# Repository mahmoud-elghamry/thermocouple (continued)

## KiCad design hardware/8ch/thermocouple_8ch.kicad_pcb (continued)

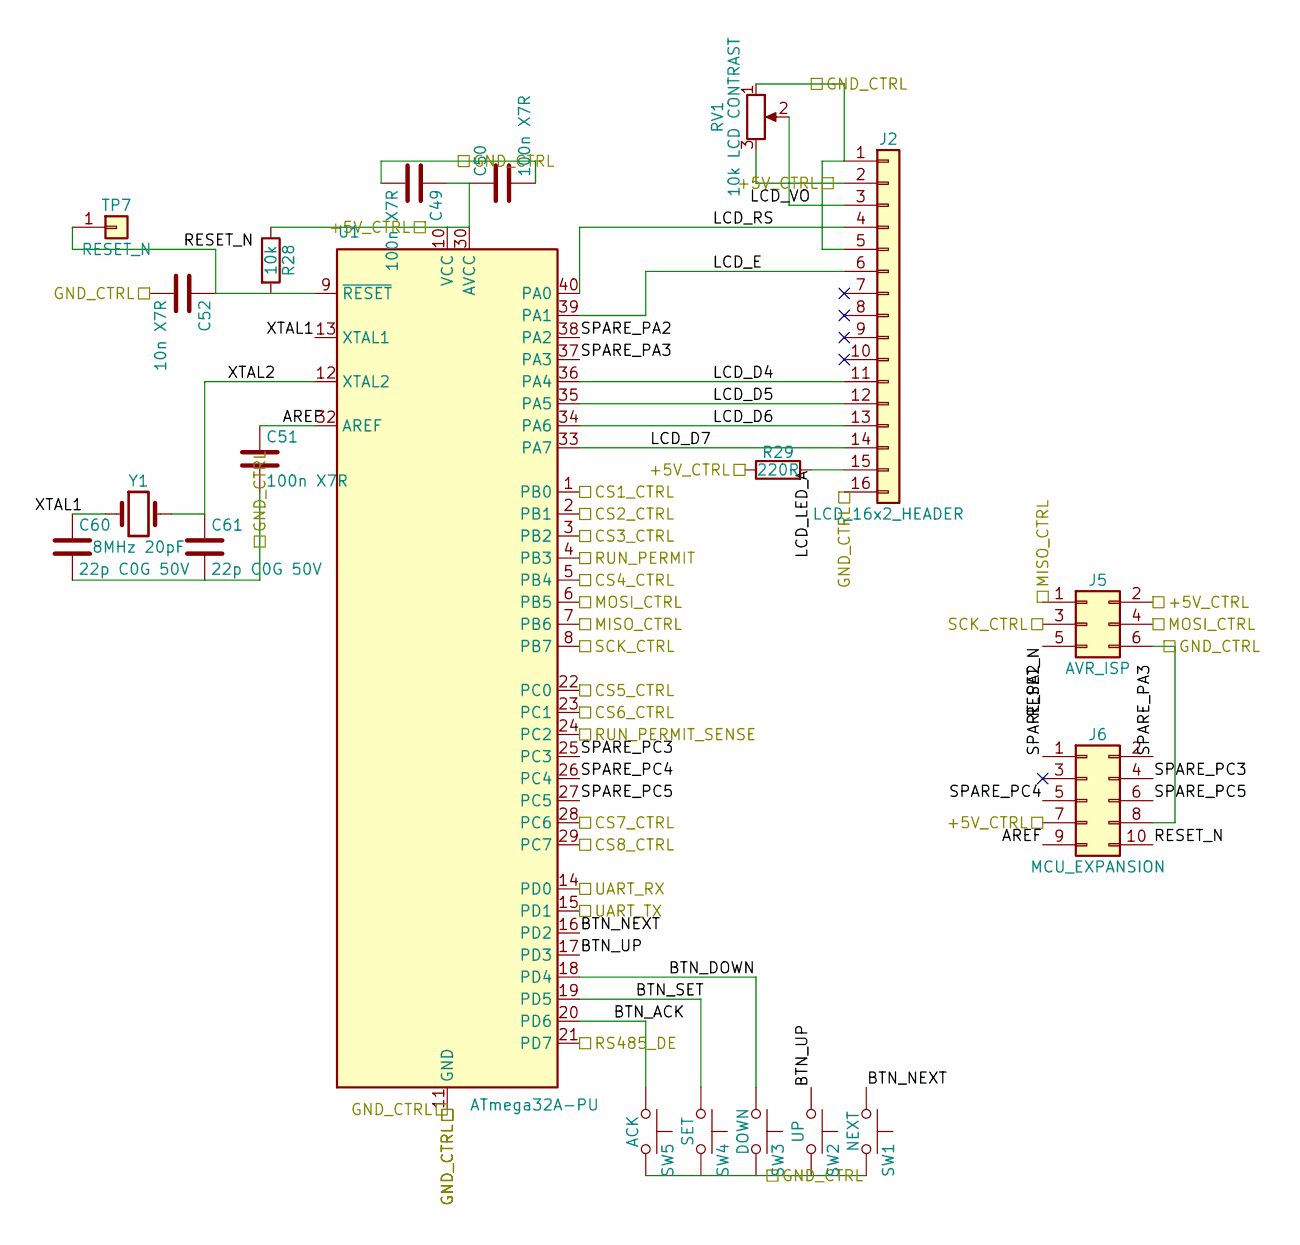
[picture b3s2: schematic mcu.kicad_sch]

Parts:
C49, C50, C51: 100n X7R; C_0805_2012Metric; MPN CC0805KRX7R9BB104; LCSC C49678
C52: 10n X7R; C_0805_2012Metric; MPN CL21B103KBANNNC; LCSC C1710
C60, C61: 22p C0G 50V; C_0805_2012Metric; MPN CL21C220JBANNNC; LCSC C1804
J2: LCD_16x2_HEADER; PinHeader_1x16_P2.54mm_Vertical; MPN ZX-PZ2.54-1-16PZZ; LCSC C7501270
J5: AVR_ISP; PinHeader_2x03_P2.54mm_Vertical; MPN PZ254V-12-6P; LCSC C492420
J6: MCU_EXPANSION; PinHeader_2x05_P2.54mm_Vertical; MPN PZ254V-12-10P; LCSC C492422
R28: 10k; R_0805_2012Metric; MPN 0805W8F1002T5E; LCSC C17414
R29: 220R; R_0805_2012Metric; MPN 0805W8F2200T5E; LCSC C17557
RV1: 10k LCD CONTRAST; Potentiometer_Bourns_3296W_Vertical; MPN 3296W-1-103LF; LCSC C34846
SW1: NEXT; SW_PUSH_6mm; MPN TS665CJ; LCSC C393938
SW2: UP; SW_PUSH_6mm; MPN TS665CJ; LCSC C393938
SW3: DOWN; SW_PUSH_6mm; MPN TS665CJ; LCSC C393938
SW4: SET; SW_PUSH_6mm; MPN TS665CJ; LCSC C393938
SW5: ACK; SW_PUSH_6mm; MPN TS665CJ; LCSC C393938
TP7: RESET_N; TestPoint_THTPad_D2.0mm_Drill1.0mm
U1: ATmega32A-PU; DIP-40_W15.24mm_Socket; MPN ATMEGA32A-PU; LCSC C12703
Y1: 8MHz 20pF; Crystal_SMD_HC49-SD; MPN X49SM8MSD2SC; LCSC C12674

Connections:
/+5V_CTRL: C49.1, C50.1, J2.2, J5.2, J6.7, R28.1, R29.1, RV1.3, U1.10 (VCC), U1.30 (AVCC); also elsewhere on the board
/CS1_CTRL: U1.1 (PB0); also elsewhere on the board
/CS2_CTRL: U1.2 (PB1); also elsewhere on the board
/CS3_CTRL: U1.3 (PB2); also elsewhere on the board
/CS4_CTRL: U1.5 (PB4); also elsewhere on the board
/CS5_CTRL: U1.22 (PC0); also elsewhere on the board
/CS6_CTRL: U1.23 (PC1); also elsewhere on the board
/CS7_CTRL: U1.28 (PC6); also elsewhere on the board
/CS8_CTRL: U1.29 (PC7); also elsewhere on the board
/GND_CTRL: C49.2, C50.2, C51.2, C52.2, C60.2, C61.2, J2.1, J2.5, J2.16, J5.6, J6.8, RV1.1, SW1.2, SW2.2, SW3.2, SW4.2, SW5.2, U1.11 (GND), U1.31 (GND); also elsewhere on the board
/MCU/AREF: C51.1, J6.9, U1.32 (AREF)
/MCU/BTN_ACK: SW5.1, U1.20 (PD6)
/MCU/BTN_DOWN: SW3.1, U1.18 (PD4)
/MCU/BTN_NEXT: SW1.1, U1.16 (PD2)
/MCU/BTN_SET: SW4.1, U1.19 (PD5)
/MCU/BTN_UP: SW2.1, U1.17 (PD3)
/MCU/LCD_D4: J2.11, U1.36 (PA4)
/MCU/LCD_D5: J2.12, U1.35 (PA5)
/MCU/LCD_D6: J2.13, U1.34 (PA6)
/MCU/LCD_D7: J2.14, U1.33 (PA7)
/MCU/LCD_E: J2.6, U1.39 (PA1)
/MCU/LCD_LED_A: J2.15, R29.2
/MCU/LCD_RS: J2.4, U1.40 (PA0)
/MCU/LCD_VO: J2.3, RV1.2
/MCU/RESET_N: C52.1, J5.5, J6.10, R28.2, TP7.1 (Pin_1_1), U1.9 (~RESET)
/MCU/SPARE_PA2: J6.1, U1.38 (PA2)
/MCU/SPARE_PA3: J6.2, U1.37 (PA3)
/MCU/SPARE_PC3: J6.4, U1.25 (PC3)
/MCU/SPARE_PC4: J6.5, U1.26 (PC4)
/MCU/SPARE_PC5: J6.6, U1.27 (PC5)
/MCU/XTAL1: C60.1, U1.13 (XTAL1), Y1.1
/MCU/XTAL2: C61.1, U1.12 (XTAL2), Y1.2
/MISO_CTRL: J5.1, U1.7 (PB6); also elsewhere on the board
/MOSI_CTRL: J5.4, U1.6 (PB5); also elsewhere on the board
/RS485_DE: U1.21 (PD7); also elsewhere on the board
/RUN_PERMIT: U1.4 (PB3); also elsewhere on the board
/RUN_PERMIT_SENSE: U1.24 (PC2); also elsewhere on the board
/SCK_CTRL: J5.3, U1.8 (PB7); also elsewhere on the board
/UART_RX: U1.14 (PD0); also elsewhere on the board
/UART_TX: U1.15 (PD1); also elsewhere on the board

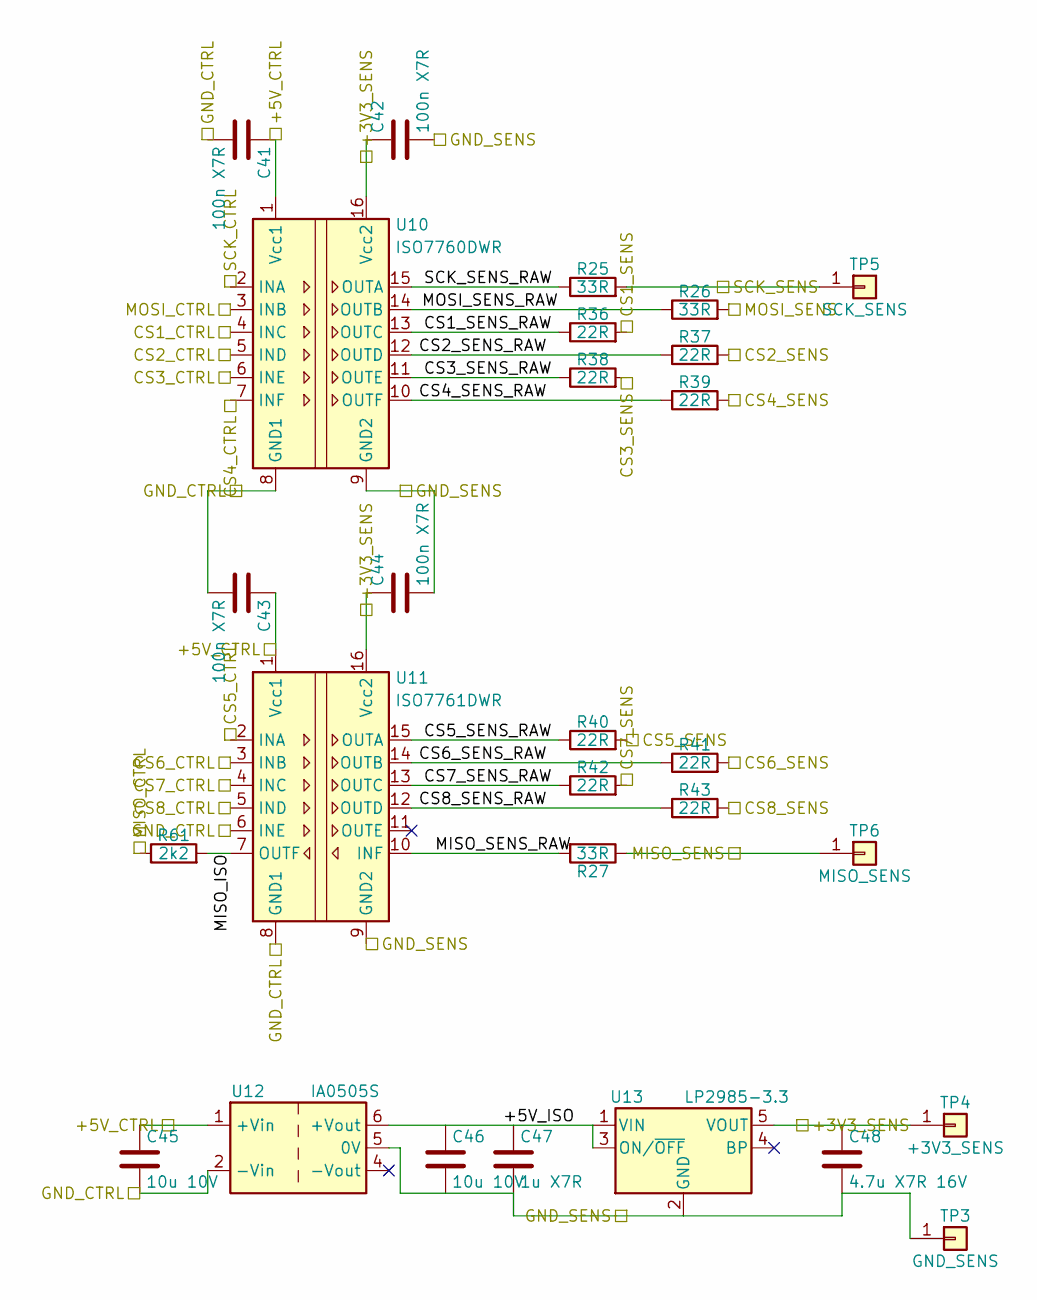
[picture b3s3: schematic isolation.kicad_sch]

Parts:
C41, C42, C43, C44: 100n X7R; C_0805_2012Metric; MPN CC0805KRX7R9BB104; LCSC C49678
C45, C46: 10u 10V; C_0805_2012Metric; MPN CL21A106KAYNNNE; LCSC C15850
C47: 1u X7R; C_0805_2012Metric; MPN CL21B105KBFNNNE; LCSC C28323
C48: 4.7u X7R 16V; C_0805_2012Metric; MPN CGA0805X7R475K350MT; LCSC C6119943
R25, R26, R27: 33R; R_0805_2012Metric; MPN 0805W8F330JT5E; LCSC C17634
R36, R37, R38, R39, R40, R41, R42, R43: 22R; R_0805_2012Metric; MPN 0805W8F220JT5E; LCSC C17561
R61: 2k2; R_0805_2012Metric; MPN 0805W8F2201T5E; LCSC C17520
TP3: GND_SENS; TestPoint_THTPad_D2.0mm_Drill1.0mm
TP4: +3V3_SENS; TestPoint_THTPad_D2.0mm_Drill1.0mm
TP5: SCK_SENS; TestPoint_THTPad_D2.0mm_Drill1.0mm
TP6: MISO_SENS; TestPoint_THTPad_D2.0mm_Drill1.0mm
U10: ISO7760DWR; SOIC-16W_7.5x10.3mm_P1.27mm; MPN ISO7760DWR; LCSC C882724
U11: ISO7761DWR; SOIC-16W_7.5x10.3mm_P1.27mm; MPN ISO7761DWR; LCSC C2871529
U12: IA0505S; Converter_DCDC_XP_POWER-IAxxxxS_THT; MPN IA0505S
U13: LP2985-3.3; SOT-23-5; MPN LP2985IM5X-3.3/NOPB

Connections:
/+3V3_SENS: C42.1, C44.1, C48.1, TP4.1 (Pin_1_1), U10.16 (Vcc2), U11.16 (Vcc2), U13.5 (VOUT); also elsewhere on the board
/+5V_CTRL: C41.1, C43.1, C45.1, U10.1 (Vcc1), U11.1 (Vcc1), U12.1 (+Vin); also elsewhere on the board
/CS1_CTRL: U10.4 (INC); also elsewhere on the board
/CS1_SENS: R36.2; also elsewhere on the board
/CS2_CTRL: U10.5 (IND); also elsewhere on the board
/CS2_SENS: R37.2; also elsewhere on the board
/CS3_CTRL: U10.6 (INE); also elsewhere on the board
/CS3_SENS: R38.2; also elsewhere on the board
/CS4_CTRL: U10.7 (INF); also elsewhere on the board
/CS4_SENS: R39.2; also elsewhere on the board
/CS5_CTRL: U11.2 (INA); also elsewhere on the board
/CS5_SENS: R40.2; also elsewhere on the board
/CS6_CTRL: U11.3 (INB); also elsewhere on the board
/CS6_SENS: R41.2; also elsewhere on the board
/CS7_CTRL: U11.4 (INC); also elsewhere on the board
/CS7_SENS: R42.2; also elsewhere on the board
/CS8_CTRL: U11.5 (IND); also elsewhere on the board
/CS8_SENS: R43.2; also elsewhere on the board
/GND_CTRL: C41.2, C43.2, C45.2, U10.8 (GND1), U11.6 (INE), U11.8 (GND1), U12.2 (-Vin); also elsewhere on the board
/GND_SENS: C42.2, C44.2, C46.2, C47.2, C48.2, TP3.1 (Pin_1_1), U10.9 (GND2), U11.9 (GND2), U12.5 (0V), U13.2 (GND); also elsewhere on the board
/ISOLATION/+5V_ISO: C46.1, C47.1, U12.6 (+Vout), U13.1 (VIN), U13.3 (ON/~OFF)
/ISOLATION/CS1_SENS_RAW: R36.1, U10.13 (OUTC)
/ISOLATION/CS2_SENS_RAW: R37.1, U10.12 (OUTD)
/ISOLATION/CS3_SENS_RAW: R38.1, U10.11 (OUTE)
/ISOLATION/CS4_SENS_RAW: R39.1, U10.10 (OUTF)
/ISOLATION/CS5_SENS_RAW: R40.1, U11.15 (OUTA)
/ISOLATION/CS6_SENS_RAW: R41.1, U11.14 (OUTB)
/ISOLATION/CS7_SENS_RAW: R42.1, U11.13 (OUTC)
/ISOLATION/CS8_SENS_RAW: R43.1, U11.12 (OUTD)
/ISOLATION/MISO_ISO: R61.2, U11.7 (OUTF)
/ISOLATION/MISO_SENS_RAW: R27.2, U11.10 (INF)
/ISOLATION/MOSI_SENS_RAW: R26.1, U10.14 (OUTB)
/ISOLATION/SCK_SENS_RAW: R25.1, U10.15 (OUTA)
/MISO_CTRL: R61.1; also elsewhere on the board
/MISO_SENS: R27.1, TP6.1 (Pin_1_1); also elsewhere on the board
/MOSI_CTRL: U10.3 (INB); also elsewhere on the board
/MOSI_SENS: R26.2; also elsewhere on the board
/SCK_CTRL: U10.2 (INA); also elsewhere on the board
/SCK_SENS: R25.2, TP5.1 (Pin_1_1); also elsewhere on the board

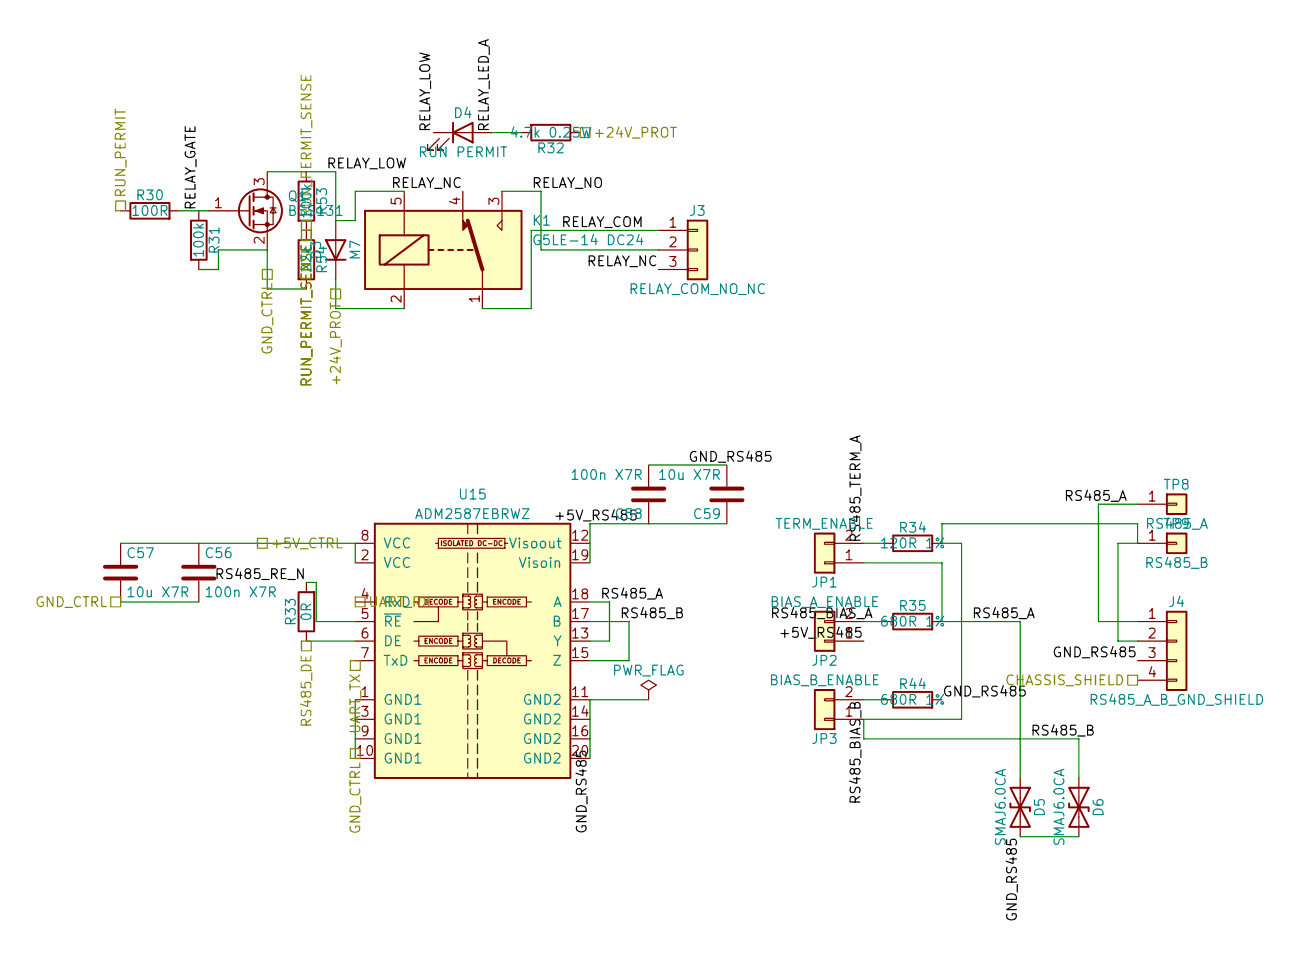
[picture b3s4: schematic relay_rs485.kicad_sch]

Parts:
C56, C58: 100n X7R; C_0805_2012Metric; MPN CC0805KRX7R9BB104; LCSC C49678
C57, C59: 10u X7R; C_0805_2012Metric; MPN CL21B106KOQNNNE; LCSC C95841
D3: M7; D_SMA; MPN M7; LCSC C95872
D4: RUN PERMIT; LED_D3.0mm; MPN 3A4GUD; LCSC C52034646
D5, D6: SMAJ6.0CA; D_SMA; MPN SMAJ6.0CA; LCSC C19077526
J3: RELAY_COM_NO_NC; TerminalBlock_Phoenix_MKDS-1,5-3_1x03_P5.00mm_Horizontal; MPN WJ128V-5.0-3P; LCSC C8270
J4: RS485_A_B_GND_SHIELD; TerminalBlock_Phoenix_MKDS-1,5-4_1x04_P5.00mm_Horizontal; MPN WJ128V-5.0-04P-14-00A; LCSC C192769
JP1: TERM_ENABLE; PinHeader_1x02_P2.54mm_Vertical; MPN PZ254V-11-02P; LCSC C492401
JP2: BIAS_A_ENABLE; PinHeader_1x02_P2.54mm_Vertical; MPN PZ254V-11-02P; LCSC C492401
JP3: BIAS_B_ENABLE; PinHeader_1x02_P2.54mm_Vertical; MPN PZ254V-11-02P; LCSC C492401
K1: G5LE-14 DC24; Relay_SPDT_Omron-G5LE-1; MPN G5LE-14 DC24; LCSC C116965
Q1: BSS131; SOT-23; MPN BSS131H6327XTSA1; LCSC C151498
R30: 100R; R_0805_2012Metric; MPN 0805W8F1000T5E; LCSC C17408
R31, R53: 100k; R_0805_2012Metric; MPN 0805W8F1003T5E; LCSC C149504
R32: 4.7k 0.25W; R_0805_2012Metric; MPN RK73H2ATTD4701F; LCSC C276229
R33: 0R; R_0805_2012Metric; MPN 0805W8F0000T5E; LCSC C17477
R34: 120R 1%; R_0805_2012Metric; MPN 0805W8F1200T5E; LCSC C17437
R35, R44: 680R 1%; R_0805_2012Metric; MPN 0805W8F6800T5E; LCSC C17798
R54: 22k; R_0805_2012Metric; MPN 0805W8F2202T5E; LCSC C17560
TP8: RS485_A; TestPoint_THTPad_D2.0mm_Drill1.0mm
TP9: RS485_B; TestPoint_THTPad_D2.0mm_Drill1.0mm
U15: ADM2587EBRWZ; SOIC-20W_7.5x12.8mm_P1.27mm; MPN ADM2587EBRWZ-REEL7; LCSC C12081

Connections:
/+5V_CTRL: C56.1, C57.1, U15.2 (VCC), U15.8 (VCC); also elsewhere on the board
/+24V_PROT: D3.1 (K), K1.2, R32.1; also elsewhere on the board
/CHASSIS_SHIELD: J4.4; also elsewhere on the board
/GND_CTRL: C56.2, C57.2, Q1.2 (S), R31.2, R54.2, U15.1 (GND1), U15.3 (GND1), U15.9 (GND1), U15.10 (GND1); also elsewhere on the board
/RELAY_RS485/+5V_RS485: C58.1, C59.1, JP2.1, U15.12 (Visoout), U15.19 (Visoin)
/RELAY_RS485/GND_RS485: C58.2, C59.2, D5.2 (A2), D6.2 (A2), J4.3, R44.2, U15.11 (GND2), U15.14 (GND2), U15.16 (GND2), U15.20 (GND2)
/RELAY_RS485/RELAY_COM: J3.1, K1.1
/RELAY_RS485/RELAY_GATE: Q1.1 (G), R30.2, R31.1
/RELAY_RS485/RELAY_LED_A: D4.2 (A), R32.2
/RELAY_RS485/RELAY_LOW: D3.2 (A), D4.1 (K), K1.5, Q1.3 (D), R53.1
/RELAY_RS485/RELAY_NC: J3.3, K1.4
/RELAY_RS485/RELAY_NO: J3.2, K1.3
/RELAY_RS485/RS485_A: D5.1 (A1), J4.1, JP1.1, R35.2, TP8.1 (Pin_1_1), U15.13 (Y), U15.18 (A)
/RELAY_RS485/RS485_B: D6.1 (A1), J4.2, JP3.1, R34.2, TP9.1 (Pin_1_1), U15.15 (Z), U15.17 (B)
/RELAY_RS485/RS485_BIAS_A: JP2.2, R35.1
/RELAY_RS485/RS485_BIAS_B: JP3.2, R44.1
/RELAY_RS485/RS485_RE_N: R33.2, U15.5 (~RE)
/RELAY_RS485/RS485_TERM_A: JP1.2, R34.1
/RS485_DE: R33.1, U15.6 (DE); also elsewhere on the board
/RUN_PERMIT: R30.1; also elsewhere on the board
/RUN_PERMIT_SENSE: R53.2, R54.1; also elsewhere on the board
/UART_RX: U15.4 (RxD); also elsewhere on the board
/UART_TX: U15.7 (TxD); also elsewhere on the board

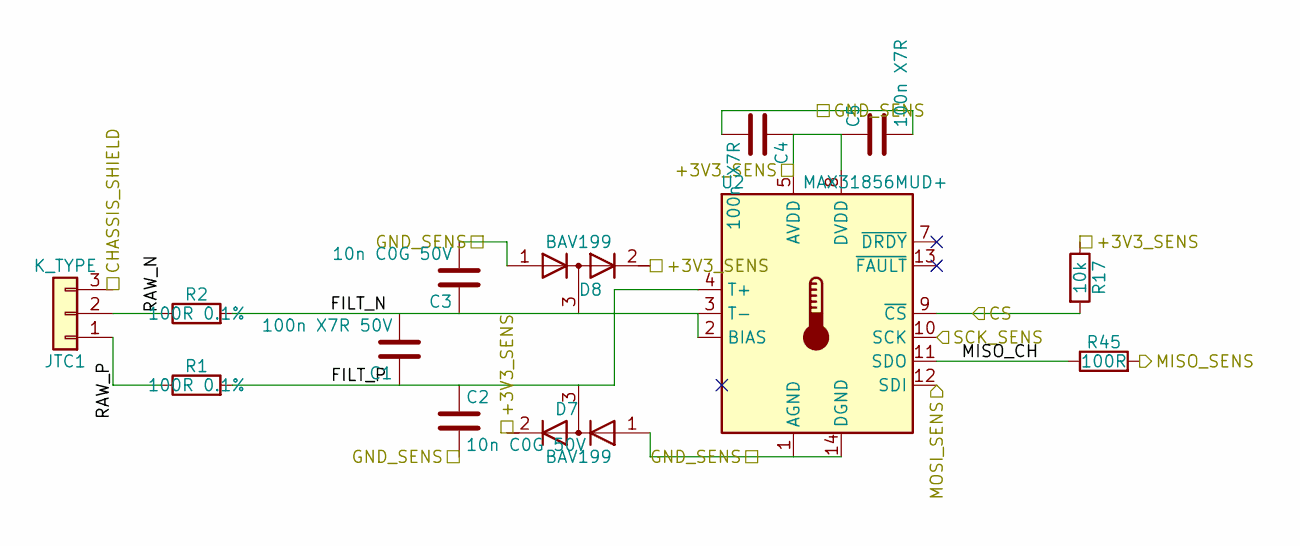
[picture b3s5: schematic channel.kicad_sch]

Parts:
C1: 100n X7R 50V; C_0805_2012Metric; MPN CC0805KRX7R9BB104; LCSC C49678
C2, C3: 10n C0G 50V; C_0805_2012Metric; MPN GRM2195C1H103JA01D; LCSC C97905
C4, C5: 100n X7R; C_0805_2012Metric; MPN CC0805KRX7R9BB104; LCSC C49678
D7, D8: BAV199; SOT-23; MPN BAV199; LCSC C5184419
JTC1: K_TYPE; TerminalBlock_Phoenix_MKDS-1,5-3_1x03_P5.00mm_Horizontal; MPN WJ128V-5.0-3P; LCSC C8270
R1, R2: 100R 0.1%; R_0805_2012Metric; MPN RT0805BRD07100RL; LCSC C110773
R17: 10k; R_0805_2012Metric; MPN 0805W8F1002T5E; LCSC C17414
R45: 100R; R_0805_2012Metric; MPN 0805W8F1000T5E; LCSC C17408
U2: MAX31856MUD+; TSSOP-14_4.4x5mm_P0.65mm; MPN MAX31856MUD+

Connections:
/+3V3_SENS: C4.1, C5.1, D7.2 (K), D8.2 (K), R17.1, U2.5 (AVDD), U2.8 (DVDD); also elsewhere on the board
/CHASSIS_SHIELD: JTC1.3; also elsewhere on the board
/CS1_SENS: R17.2, U2.9 (~CS); also elsewhere on the board
/GND_SENS: C2.2, C3.2, C4.2, C5.2, D7.1 (A), D8.1 (A), U2.1 (AGND), U2.14 (DGND); also elsewhere on the board
/MISO_SENS: R45.2; also elsewhere on the board
/MOSI_SENS: U2.12 (SDI); also elsewhere on the board
/SCK_SENS: U2.10 (SCK); also elsewhere on the board
/TC1/FILT_N: C1.2, C3.1, D8.3 (common), R2.2, U2.2 (BIAS), U2.3 (T-)
/TC1/FILT_P: C1.1, C2.1, D7.3 (common), R1.2, U2.4 (T+)
/TC1/MISO_CH: R45.1, U2.11 (SDO)
/TC1/RAW_N: JTC1.2, R2.1
/TC1/RAW_P: JTC1.1, R1.1

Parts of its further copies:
C6, C11, C16, C21, C26, C31, C36: 100n X7R 50V; C_0805_2012Metric; MPN CC0805KRX7R9BB104; LCSC C49678
C7, C8, C12, C13, C17, C18, C22, C23, C27, C28, C32, C33, C37, C38: 10n C0G 50V; C_0805_2012Metric; MPN GRM2195C1H103JA01D; LCSC C97905
C9, C10, C14, C15, C19, C20, C24, C25, C29, C30, C34, C35, C39, C40: 100n X7R; C_0805_2012Metric; MPN CC0805KRX7R9BB104; LCSC C49678
D9, D10, D11, D12, D13, D14, D15, D16, D17, D18, D19, D20, D21, D22: BAV199; SOT-23; MPN BAV199; LCSC C5184419
JTC2, JTC3, JTC4, JTC5, JTC6, JTC7, JTC8: K_TYPE; TerminalBlock_Phoenix_MKDS-1,5-3_1x03_P5.00mm_Horizontal; MPN WJ128V-5.0-3P; LCSC C8270
R3, R4, R5, R6, R7, R8, R9, R10, R11, R12, R13, R14, R15, R16: 100R 0.1%; R_0805_2012Metric; MPN RT0805BRD07100RL; LCSC C110773
R18, R19, R20, R21, R22, R23, R24: 10k; R_0805_2012Metric; MPN 0805W8F1002T5E; LCSC C17414
R46, R47, R48, R49, R50, R51, R52: 100R; R_0805_2012Metric; MPN 0805W8F1000T5E; LCSC C17408
U3, U4, U5, U6, U7, U8, U9: MAX31856MUD+; TSSOP-14_4.4x5mm_P0.65mm; MPN MAX31856MUD+

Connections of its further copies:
/+3V3_SENS: C9.1, C10.1, C14.1, C15.1, C19.1, C20.1, C24.1, C25.1, C29.1, C30.1, C34.1, C35.1, C39.1, C40.1, D9.2 (K), D10.2 (K), D11.2 (K), D12.2 (K), D13.2 (K), D14.2 (K), D15.2 (K), D16.2 (K), D17.2 (K), D18.2 (K), D19.2 (K), D20.2 (K), D21.2 (K), D22.2 (K), R18.1, R19.1, R20.1, R21.1, R22.1, R23.1, R24.1, U3.5 (AVDD), U3.8 (DVDD), U4.5 (AVDD), U4.8 (DVDD), U5.5 (AVDD), U5.8 (DVDD), U6.5 (AVDD), U6.8 (DVDD), U7.5 (AVDD), U7.8 (DVDD), U8.5 (AVDD), U8.8 (DVDD), U9.5 (AVDD), U9.8 (DVDD); also elsewhere on the board
/CHASSIS_SHIELD: JTC2.3, JTC3.3, JTC4.3, JTC5.3, JTC6.3, JTC7.3, JTC8.3; also elsewhere on the board
/CS2_SENS: R18.2, U3.9 (~CS); also elsewhere on the board
/CS3_SENS: R19.2, U4.9 (~CS); also elsewhere on the board
/CS4_SENS: R20.2, U5.9 (~CS); also elsewhere on the board
/CS5_SENS: R21.2, U6.9 (~CS); also elsewhere on the board
/CS6_SENS: R22.2, U7.9 (~CS); also elsewhere on the board
/CS7_SENS: R23.2, U8.9 (~CS); also elsewhere on the board
/CS8_SENS: R24.2, U9.9 (~CS); also elsewhere on the board
/GND_SENS: C7.2, C8.2, C9.2, C10.2, C12.2, C13.2, C14.2, C15.2, C17.2, C18.2, C19.2, C20.2, C22.2, C23.2, C24.2, C25.2, C27.2, C28.2, C29.2, C30.2, C32.2, C33.2, C34.2, C35.2, C37.2, C38.2, C39.2, C40.2, D9.1 (A), D10.1 (A), D11.1 (A), D12.1 (A), D13.1 (A), D14.1 (A), D15.1 (A), D16.1 (A), D17.1 (A), D18.1 (A), D19.1 (A), D20.1 (A), D21.1 (A), D22.1 (A), U3.1 (AGND), U3.14 (DGND), U4.1 (AGND), U4.14 (DGND), U5.1 (AGND), U5.14 (DGND), U6.1 (AGND), U6.14 (DGND), U7.1 (AGND), U7.14 (DGND), U8.1 (AGND), U8.14 (DGND), U9.1 (AGND), U9.14 (DGND); also elsewhere on the board
/MISO_SENS: R46.2, R47.2, R48.2, R49.2, R50.2, R51.2, R52.2; also elsewhere on the board
/MOSI_SENS: U3.12 (SDI), U4.12 (SDI), U5.12 (SDI), U6.12 (SDI), U7.12 (SDI), U8.12 (SDI), U9.12 (SDI); also elsewhere on the board
/SCK_SENS: U3.10 (SCK), U4.10 (SCK), U5.10 (SCK), U6.10 (SCK), U7.10 (SCK), U8.10 (SCK), U9.10 (SCK); also elsewhere on the board
/TC2/FILT_N: C6.2, C8.1, D10.3 (common), R4.2, U3.2 (BIAS), U3.3 (T-)
/TC2/FILT_P: C6.1, C7.1, D9.3 (common), R3.2, U3.4 (T+)
/TC2/MISO_CH: R46.1, U3.11 (SDO)
/TC2/RAW_N: JTC2.2, R4.1
/TC2/RAW_P: JTC2.1, R3.1
/TC3/FILT_N: C11.2, C13.1, D12.3 (common), R6.2, U4.2 (BIAS), U4.3 (T-)
/TC3/FILT_P: C11.1, C12.1, D11.3 (common), R5.2, U4.4 (T+)
/TC3/MISO_CH: R47.1, U4.11 (SDO)
/TC3/RAW_N: JTC3.2, R6.1
/TC3/RAW_P: JTC3.1, R5.1
/TC4/FILT_N: C16.2, C18.1, D14.3 (common), R8.2, U5.2 (BIAS), U5.3 (T-)
/TC4/FILT_P: C16.1, C17.1, D13.3 (common), R7.2, U5.4 (T+)
/TC4/MISO_CH: R48.1, U5.11 (SDO)
/TC4/RAW_N: JTC4.2, R8.1
/TC4/RAW_P: JTC4.1, R7.1
/TC5/FILT_N: C21.2, C23.1, D16.3 (common), R10.2, U6.2 (BIAS), U6.3 (T-)
/TC5/FILT_P: C21.1, C22.1, D15.3 (common), R9.2, U6.4 (T+)
/TC5/MISO_CH: R49.1, U6.11 (SDO)
/TC5/RAW_N: JTC5.2, R10.1
/TC5/RAW_P: JTC5.1, R9.1
/TC6/FILT_N: C26.2, C28.1, D18.3 (common), R12.2, U7.2 (BIAS), U7.3 (T-)
/TC6/FILT_P: C26.1, C27.1, D17.3 (common), R11.2, U7.4 (T+)
/TC6/MISO_CH: R50.1, U7.11 (SDO)
/TC6/RAW_N: JTC6.2, R12.1
/TC6/RAW_P: JTC6.1, R11.1
/TC7/FILT_N: C31.2, C33.1, D20.3 (common), R14.2, U8.2 (BIAS), U8.3 (T-)
/TC7/FILT_P: C31.1, C32.1, D19.3 (common), R13.2, U8.4 (T+)
/TC7/MISO_CH: R51.1, U8.11 (SDO)
/TC7/RAW_N: JTC7.2, R14.1
/TC7/RAW_P: JTC7.1, R13.1
/TC8/FILT_N: C36.2, C38.1, D22.3 (common), R16.2, U9.2 (BIAS), U9.3 (T-)
/TC8/FILT_P: C36.1, C37.1, D21.3 (common), R15.2, U9.4 (T+)
/TC8/MISO_CH: R52.1, U9.11 (SDO)
/TC8/RAW_N: JTC8.2, R16.1
/TC8/RAW_P: JTC8.1, R15.1

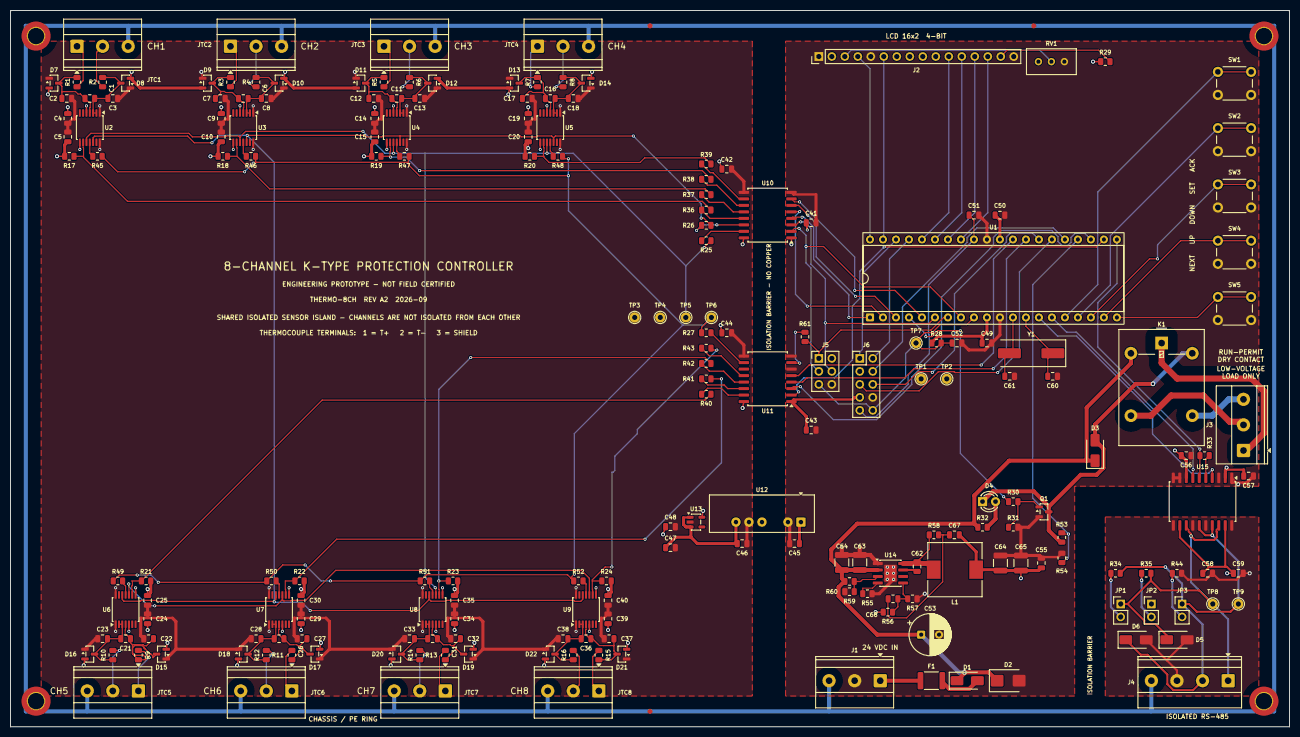
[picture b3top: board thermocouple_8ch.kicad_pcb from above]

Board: 4 copper layers, 250.0 x 140.0 mm, 209 parts (0 on the bottom side), 130 nets.

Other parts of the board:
FID1: FID1; Fiducial_1mm_Mask2mm
FID2: FID2; Fiducial_1mm_Mask2mm
FID3: FID3; Fiducial_1mm_Mask2mm
H1: H1; MountingHole_3.2mm_M3_ISO7380_Pad_TopBottom
H2: H2; MountingHole_3.2mm_M3_ISO7380_Pad_TopBottom
H3: H3; MountingHole_3.2mm_M3_ISO7380_Pad_TopBottom
H4: H4; MountingHole_3.2mm_M3_ISO7380_Pad_TopBottom

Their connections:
/CHASSIS_SHIELD: H1.1, H2.1, H3.1, H4.1; also elsewhere on the board

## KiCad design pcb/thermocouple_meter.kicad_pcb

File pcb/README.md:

# Thermocouple meter PCB

Editable two-layer KiCad 10 PCB for an ATmega32A, MAX31856, off-board 16x2
LCD, alarm LED and 5 V SPDT relay. The board is 150 x 70 mm. It accepts a
regulated 5 V input and makes 3.3 V locally with an AMS1117-3.3. The MCU and
MAX31856 run at 3.3 V; the LCD runs at 5 V.

The thermocouple front end follows the MAX31856 application guidance:

- BIAS is connected to T-.
- Matched 100 ohm series resistors are fitted in T+ and T-.
- 100 nF is fitted differentially across T+ and T-.
- 10 nF common-mode capacitors are fitted from each input to ground.
- 100 nF local bypass capacitors are fitted at AVDD and DVDD.

Generate the PCB from the deterministic Python source, run DRC, then export
Gerbers, drill files, PDF and 3D previews:

```powershell
& 'C:\Program Files\KiCad\10.0\bin\python.exe' .\generate_board.py
& .\build_outputs.ps1
```

J2 is a standard 16-pin HD44780 LCD header. J4 is a 6-pin AVR ISP header.
The ATmega32 uses its internal 8 MHz clock, so no crystal is required.

PB3 (DIP pin 4) drives Q1 through R4; Q1 switches the K1 coil. D1 clamps the
coil flyback voltage, R5 keeps the relay off during reset, and D2/R6 indicate
the output state. J5 exposes COM/NO/NC. This contact area is intended only for
low-voltage loads in this revision; it is not documented or certified for mains.

## Delivered fabrication files

- `thermocouple_meter.kicad_pcb`: editable KiCad 10 board.
- `drc-report.txt`: zero violations and zero unconnected pads.
- `gerbers/`: copper, solder-mask, silkscreen, outline and drill files.
- `output/thermocouple_meter_gerbers.zip`: fabrication archive.
- `output/thermocouple_meter_layers.pdf`: printable layer plots.
- `output/positions.csv`: component positions.
- `output/pcb_top.png`, `pcb_bottom.png`, `pcb_isometric.png`: 3D previews.
- `output/kicad_happy_pcb_analysis.json`: extra PCB/DFM analysis.
- `output/kicad_happy_gerber_analysis.json`: extra Gerber analysis.

Three global fiducials are included. The router also forbids layer changes in
pad keepouts, eliminating the via-in-pad warnings found during the additional
DFM pass. The remaining PCB-analyzer warning is low test-point coverage, which
is accepted for this hand-assembled educational revision.

This board is for the **MAX31856 final hardware**. MAX6675 is used only as a
Proteus fallback and is not a pin-compatible replacement for MAX31856.

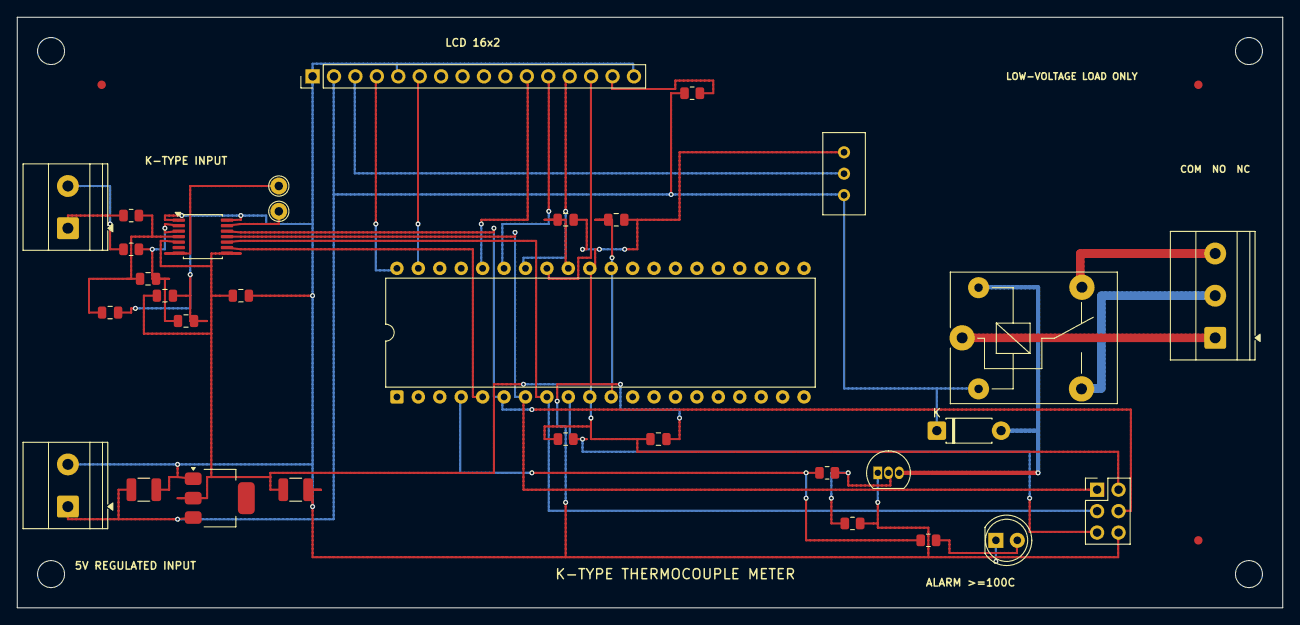
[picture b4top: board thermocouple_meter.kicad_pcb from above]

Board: 2 copper layers, 150.0 x 70.0 mm, 39 parts (0 on the bottom side), 30 nets.

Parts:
C1, C2: 10uF 10V; C_1210_3225Metric
C3: 100nF MCU VCC; C_0805_2012Metric
C4: 100nF MCU AVCC; C_0805_2012Metric
C5: 100nF MAX AVDD; C_0805_2012Metric
C6: 100nF MAX DVDD; C_0805_2012Metric
C7: 100nF TC DIFF; C_0805_2012Metric
C8: 10nF TC+; C_0805_2012Metric
C9: 10nF TC-; C_0805_2012Metric
C10: 100nF AREF; C_0805_2012Metric
D1: 1N4007 FLYBACK; D_DO-41_SOD81_P7.62mm_Horizontal
D2: ALARM LED; LED_D5.0mm_Clear
FID1, FID2, FID3: FIDUCIAL; Fiducial_1mm_Mask2mm
H1, H2, H3, H4: M3; MountingHole_3.2mm_M3
J1: 5V_INPUT; TerminalBlock_Phoenix_MKDS-1,5-2_1x02_P5.00mm_Horizontal
J2: LCD_16x2; PinHeader_1x16_P2.54mm_Vertical
J3: K-TYPE; TerminalBlock_Phoenix_MKDS-1,5-2_1x02_P5.00mm_Horizontal
J4: AVR_ISP; PinHeader_2x03_P2.54mm_Vertical
J5: RELAY_COM_NO_NC; TerminalBlock_Phoenix_MKDS-1,5-3_1x03_P5.00mm_Horizontal
K1: SRD-05VDC-SL-C; Relay_SPDT_SANYOU_SRD_Series_Form_C
Q1: 2N3904 E-B-C; TO-92_Inline
R1, R2: 100R 0.1%; R_0805_2012Metric
R3: 10k RESET; R_0805_2012Metric
R4: 1k RELAY BASE; R_0805_2012Metric
R5: 10k BASE PULLDOWN; R_0805_2012Metric
R6: 1k ALARM LED; R_0805_2012Metric
R7: 100R LCD LED; R_0805_2012Metric
RV1: 10k LCD CONTRAST; Potentiometer_Bourns_3296W_Vertical
TP1: DRDY; TestPoint_THTPad_D2.0mm_Drill1.0mm
TP2: FAULT; TestPoint_THTPad_D2.0mm_Drill1.0mm
U1: ATmega32A-PU; DIP-40_W15.24mm
U2: MAX31856MUD+; TSSOP-14_4.4x5mm_P0.65mm
U3: AMS1117-3.3; SOT-223-3_TabPin2

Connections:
+3V3: C2.1, C3.1, C4.1, C5.1, C6.1, J4.2, R3.1, U1.10, U1.30, U2.5, U2.8, U3.2
+5V: C1.1, D1.1, J1.1, J2.2, K1.2, R7.1, RV1.3, U3.3
ALARM_BASE: Q1.2, R4.2, R5.1
ALARM_GPIO: R4.1, R6.1, U1.4
ALARM_LED_A: D2.2, R6.2
AREF: C10.1, U1.32
GND: C1.2, C2.2, C3.2, C4.2, C5.2, C6.2, C8.2, C9.2, C10.2, D2.1, J1.2, J2.1, J2.5, J2.16, J4.6, Q1.1, R5.2, RV1.1, U1.11, U1.31, U2.1, U2.14, U3.1
LCD_D4: J2.11, U1.36
LCD_D5: J2.12, U1.35
LCD_D6: J2.13, U1.34
LCD_D7: J2.14, U1.33
LCD_E: J2.6, U1.39
LCD_LED_A: J2.15, R7.2
LCD_RS: J2.4, U1.40
LCD_VO: J2.3, RV1.2
MAX_DRDY: TP1.1, U2.7
MAX_FAULT: TP2.1, U2.13
RELAY_COM: J5.1, K1.1
RELAY_LOW: D1.2, K1.5, Q1.3
RELAY_NC: J5.3, K1.4
RELAY_NO: J5.2, K1.3
RESET: J4.5, R3.2, U1.9
SPI_CS: U1.5, U2.9
SPI_MISO: J4.1, U1.7, U2.11
SPI_MOSI: J4.4, U1.6, U2.12
SPI_SCK: J4.3, U1.8, U2.10
TC_MINUS: C7.2, C9.1, R2.2, U2.2, U2.3
TC_PLUS: C7.1, C8.1, R1.2, U2.4
TC_RAW_MINUS: J3.2, R2.1
TC_RAW_PLUS: J3.1, R1.1

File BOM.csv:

Reference,Quantity,Value,Package,Notes
U1,1,ATmega32A-PU,DIP-40,Internal 8 MHz clock
U2,1,MAX31856MUD+,TSSOP-14,Precision thermocouple converter
U3,1,AMS1117-3.3,SOT-223,3.3 V regulator
J1,1,5V regulated input,2-pin 5.00mm terminal block,Observe polarity
J2,1,LCD 16x2,1x16 2.54mm header,HD44780-compatible
J3,1,K-type thermocouple,2-pin 5.00mm terminal block,Use thermocouple-compatible connector if accuracy is critical
J4,1,AVR ISP,2x3 2.54mm header,3.3 V programming
J5,1,Relay contacts,3-pin 5.00mm terminal block,COM / NO / NC; low-voltage loads only
RV1,1,10k,3296W trimmer,LCD contrast
R1 R2,2,100R 0.1%,0805,Matched thermocouple input resistors
R3,1,10k,0805,RESET pull-up
R4,1,1k,0805,Q1 base current limit
R5,1,10k,0805,Q1 base pull-down keeps relay off during reset
R6,1,1k,0805,Alarm LED current limit
R7,1,100R,0805,LCD backlight current limit
C1 C2,2,10uF 10V,1210,Regulator input/output
C3 C4 C5 C6 C10,5,100nF,0805,Supply and AREF bypass
C7,1,100nF C0G,0805,Differential thermocouple filter
C8 C9,2,10nF C0G,0805,Common-mode thermocouple filter
TP1 TP2,2,Test point,THT 2mm,DRDY and FAULT
Q1,1,2N3904,TO-92 E-B-C,Relay low-side driver; verify the purchased part pinout
D1,1,1N4007,DO-41,Flyback diode across relay coil
D2,1,Alarm LED,LED 5mm,Lights when PB3 alarm output is active
K1,1,SRD-05VDC-SL-C,Songle SRD SPDT THT,5 V coil; footprint and contact ratings must match purchased relay
H1 H2 H3 H4,4,M3 mounting hole,3.2mm drill,

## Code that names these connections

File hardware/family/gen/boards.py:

"""Board data only; circuit blocks remain plain functions (owner's 0039 brief)."""
from dataclasses import dataclass, replace
from pathlib import Path

NC = "<NC>"
MCU24 = {
    "PB0": "CS_ADC2", "PB1": "CS_ADC3", "PB2": "CS_CJ1", "PB3": "RUN_PERMIT",
    "PB4": "CS_ADC1", "PB5": "MOSI", "PB6": "MISO", "PB7": "SCK",
    "PC0": "CS_CJ2", "PC1": "CS_CJ3", "PC2": "RUN_SENSE", "PC3": "CS_CJ4",
    "PC4": "CS_CJ5", "PC5": "CS_CJ6", "PC6": "ALARM_DRIVE", "PC7": "ALARM_SENSE",
    "PD0": "UART_RX", "PD1": "UART_TX", "PD2": "BTN_UP", "PD3": "BTN_DOWN",
    "PD4": "BTN_SET", "PD5": "BTN_ESC", "PD6": "BTN_ACK", "PD7": "RS485_DE",
    "PA0": "LCD_RS", "PA1": "LCD_E", "PA2": "REFOK", "PA3": "REFTEST",
    "PA4": "LCD_D4", "PA5": "LCD_D5", "PA6": "LCD_D6", "PA7": "LCD_D7",
    "~{RESET}": "RESET_N", "XTAL1": "XTAL1", "XTAL2": "XTAL2", "AREF": "AREF",
    "VCC": "+5V", "AVCC": "+5V", "GND": "GND",
}


@dataclass(frozen=True)
class Isolator:
    ref: str
    forward_in: tuple
    reverse_out: str
    forward_out: tuple
    reverse_in: str
    caps: tuple


@dataclass(frozen=True)
class Board:
    key: str
    project: str
    root_title: str
    library: str
    bank_count: int
    bank_letters: tuple
    mcu_pins: dict
    chip_selects: tuple
    cs_pullups: tuple                  # (reference, control-side net)
    isolators: tuple
    mounting_holes: tuple             # (number, kind: island/chassis/lcd/plain)
    output_folder: Path
    revision: str
    isolator_title: str
    bank_bases: tuple = (100, 200, 300)   # reference base per bank; 4xx-7xx belong to isolation/MCU/power/outputs
    sio_driver: bool = False              # 0039: gated TMP126 SIO driver instead of R443 22k (I-124)
    decoder: bool = False                 # 0039 D3: 74HC154 chip-select decoder on the island
    rtd: bool = False                     # 0039 D5: RTD bank (four 3-wire PT100)
    sync_tied: bool = False               # 0039 P8: AD7124 SYNC tied to +3V3_ISO, no 10k pull-up
    sio_a4: bool = False                  # 0041: 24-ch SIO driver descriptions (different bus loading)
    esc_diodes: bool = False              # 0041: ESC pulls UP/DOWN low; PD5 is available for SIO_WR_N

    @property
    def channel_count(self):
        return 8 * self.bank_count


CS24 = ("CS_ADC1", "CS_ADC2", "CS_ADC3") + tuple(f"CS_CJ{i}" for i in range(1, 7))
HOLES = tuple((i, "island") for i in (1, 2, 3, 10)) + ((4, "chassis"), (5, "chassis"))
HOLES += tuple((i, "lcd") for i in range(6, 10))
OUT = Path(__file__).resolve().parents[1] / "out"
B24 = Board(
    "24", "thermo24", "Thermo 24-channel protection unit - REV A4", "thermo24",
    3, tuple("ABC"), dict(MCU24, PD5="SIO_WR_N"), CS24,
    tuple((f"R{430+i}", n) for i, n in enumerate(CS24 + ("SIO_WR_N",))),
    (
        Isolator("U403", ("SCK", "MOSI", "CS_ADC1", "CS_ADC2", "CS_ADC3"), "MISO_ISO",
                 ("SCLK_ISO_RAW", "DIN_ISO_RAW", "CS_ADC1_ISO", "CS_ADC2_ISO", "CS_ADC3_ISO"),
                 "DOUT_ISO_RAW", ("C407", "C408")),
        Isolator("U404", tuple(f"CS_CJ{i}" for i in range(1, 6)), "REFOK",
                 tuple(f"CS_CJ{i}_ISO" for i in range(1, 6)), "REFOK_ISO", ("C409", "C410")),
        Isolator("U405", ("CS_CJ6", "REFTEST", "SIO_WR_N", "GND", "GND"), NC,
                 ("CS_CJ6_ISO", "REFTEST_ISO", "SIO_WR_N_ISO", NC, NC), "GND_ISO", ("C411", "C412")),
    ), HOLES, OUT / "24", "A4", "Digital isolators: SPI to the three AD7124 and six TMP126",
    sio_driver=True, sio_a4=True, esc_diodes=True,
)
CS8 = ("CS_ADC1", "CS_CJ1", "CS_CJ2")
B8 = replace(
    B24, key="8", project="thermo8", library="thermo8", revision="B0",
    root_title="Thermo 8-channel protection unit - REV B0", bank_count=1, bank_letters=("A",),
    mcu_pins={p: ("SIO_WR_N" if p == "PC1" else NC if n in set(CS24) - set(CS8) else n)
              for p, n in MCU24.items()},
    chip_selects=CS8,
    cs_pullups=(("R430", "CS_ADC1"), ("R433", "CS_CJ1"), ("R434", "CS_CJ2"), ("R439", "SIO_WR_N")),
    isolators=(
        Isolator("U403", ("SCK", "MOSI", "CS_ADC1", "CS_CJ1", "CS_CJ2"), "MISO_ISO",
                 ("SCLK_ISO_RAW", "DIN_ISO_RAW", "CS_ADC1_ISO", "CS_CJ1_ISO", "CS_CJ2_ISO"),
                 "DOUT_ISO_RAW", ("C407", "C408")),
        Isolator("U404", ("REFTEST", "SIO_WR_N", "GND", "GND", "GND"), "REFOK",
                 ("REFTEST_ISO", "SIO_WR_N_ISO", NC, NC, NC), "REFOK_ISO", ("C409", "C410")),
    ), output_folder=OUT / "8", isolator_title="Digital isolators: SPI to one AD7124 and two TMP126",
    sio_driver=True, sync_tied=True, sio_a4=False, esc_diodes=False,
    # H4 plain NPTH: on the 8-ch a CHASSIS track to it crossed the relay contacts; H5 + J601 bond CHASSIS
    mounting_holes=tuple((i, "plain") if i == 4 else (i, k) for i, k in HOLES),
)
# 40-ch (0039): chip selects decoded on the island; MCU drives A0-A3 + EN (5 pins instead of 16)
MCU40 = dict(MCU24, PB0="CSA0", PB1="CSA1", PB2="CSA2", PB4="CS_EN", PC0="CSA3", PC1="SIO_WR_N",
             PC3=NC, PC4=NC, PC5=NC)
B40 = replace(
    B24, key="40", project="thermo40", library="thermo40", revision="A0",
    root_title="Thermo 40-channel protection unit, 3 PT100 + check resistor - REV A0", bank_count=5,
    bank_letters=tuple("ABCDE"), bank_bases=(100, 200, 300, 800, 900), mcu_pins=MCU40,
    chip_selects=("CS_EN",), cs_pullups=(("R430", "CS_EN"), ("R439", "SIO_WR_N")),
    isolators=(
        Isolator("U403", ("SCK", "MOSI", "CSA0", "CSA1", "CSA2"), "MISO_ISO",
                 ("SCLK_ISO_RAW", "DIN_ISO_RAW", "CSA0_ISO", "CSA1_ISO", "CSA2_ISO"),
                 "DOUT_ISO_RAW", ("C407", "C408")),
        Isolator("U404", ("CSA3", "CS_EN", "REFTEST", "SIO_WR_N", "GND"), "REFOK",
                 ("CSA3_ISO", "CS_EN_ISO", "REFTEST_ISO", "SIO_WR_N_ISO", NC), "REFOK_ISO", ("C409", "C410")),
    ), output_folder=OUT / "40",
    isolator_title="Digital isolators: SPI, chip-select address and enable for six AD7124 and ten TMP126",
    sio_driver=True, decoder=True, rtd=True, sync_tied=True, sio_a4=False, esc_diodes=False,
)
BOARDS = {b.key: b for b in (B24, B8, B40)}

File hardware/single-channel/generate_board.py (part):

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fp("Connector_PinHeader_2.54mm", "PinHeader_2x03_P2.54mm_Vertical", "J4", "AVR_ISP", 128, 56)
fp("Potentiometer_THT", "Potentiometer_Bourns_3296W_Vertical", "RV1", "10k LCD CONTRAST", 98, 16, 90)

# 100 C alarm output.  PB3 drives both a status LED and a protected 5 V relay.
fp("Relay_THT", "Relay_SPDT_SANYOU_SRD_Series_Form_C", "K1", "SRD-05VDC-SL-C", 112, 38)
fp("TerminalBlock_Phoenix", "TerminalBlock_Phoenix_MKDS-1,5-3_1x03_P5.00mm_Horizontal",
   "J5", "RELAY_COM_NO_NC", 142, 38, 90)
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    "LCD_D7": [("U1", "33"), ("J2", "14")],
    "LCD_LED_A": [("R7", "2"), ("J2", "15")],
    "AREF": [("U1", "32"), ("C10", "1")],
    "ALARM_GPIO": [("U1", "4"), ("R4", "1"), ("R6", "1")],
    "ALARM_BASE": [("R4", "2"), ("R5", "1"), ("Q1", "2")],
    "RELAY_LOW": [("Q1", "3"), ("K1", "5"), ("D1", "2")],
    "ALARM_LED_A": [("R6", "2"), ("D2", "2")],
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    "SPI_SCK", "SPI_MISO", "SPI_MOSI", "SPI_CS", "+3V3", "+5V",
    "LCD_LED_A", "LCD_VO", "MAX_DRDY", "MAX_FAULT", "RESET", "AREF",
    "LCD_RS", "LCD_E", "LCD_D4", "LCD_D5", "LCD_D6", "LCD_D7",
    "ALARM_GPIO", "ALARM_BASE", "RELAY_LOW", "ALARM_LED_A",
    "GND",
]

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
